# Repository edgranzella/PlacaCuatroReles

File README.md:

# Placa Cuatro Relés - Hardware y PCB 🚀

Este repositorio contiene el diseño completo de la placa de circuito impreso (PCB) desarrollado en **KiCad** para un sistema de conmutación y control de potencia de **4 canales de relés**.

---

## 📌 Características del Diseño
* **Canales de Potencia:** 4 relés independientes con aislamiento optoacoplado para proteger la etapa de control.
* **Bornes de Conexión:** Bloques de terminales de tornillo (Terminal Blocks) robustos para salidas de alta corriente (NA / NC / COM).
* **Etapa de Disparo:** Transistores/Optoacopladores dedicados por canal con diodos de libre circulación (flyback) integrados.
* **Indicadores Visuales:** LEDs de estado montados en placa para retroalimentación visual de la activación de cada canal.

---

## 🛠️ Especificaciones Técnicas de Fabricación
Configuración sugerida en base a las reglas de diseño (DRC) aplicadas en KiCad:

| Parámetro | Configuración Sugerida |
| :--- | :--- |
| **Capas (Layers)** | 2 Capas |
| **Grosor de la Placa** | 1.6 mm |
| **Ancho de Pistas** | Señales estándar / Pistas de potencia reforzadas |
| **Acabado Superficial** | HASL (with lead) o ENIG |

---

## 👥 Desarrollado por
* **Damian Granzella** - *Ingeniería de Hardware* - [edgranzella](https://github.com)

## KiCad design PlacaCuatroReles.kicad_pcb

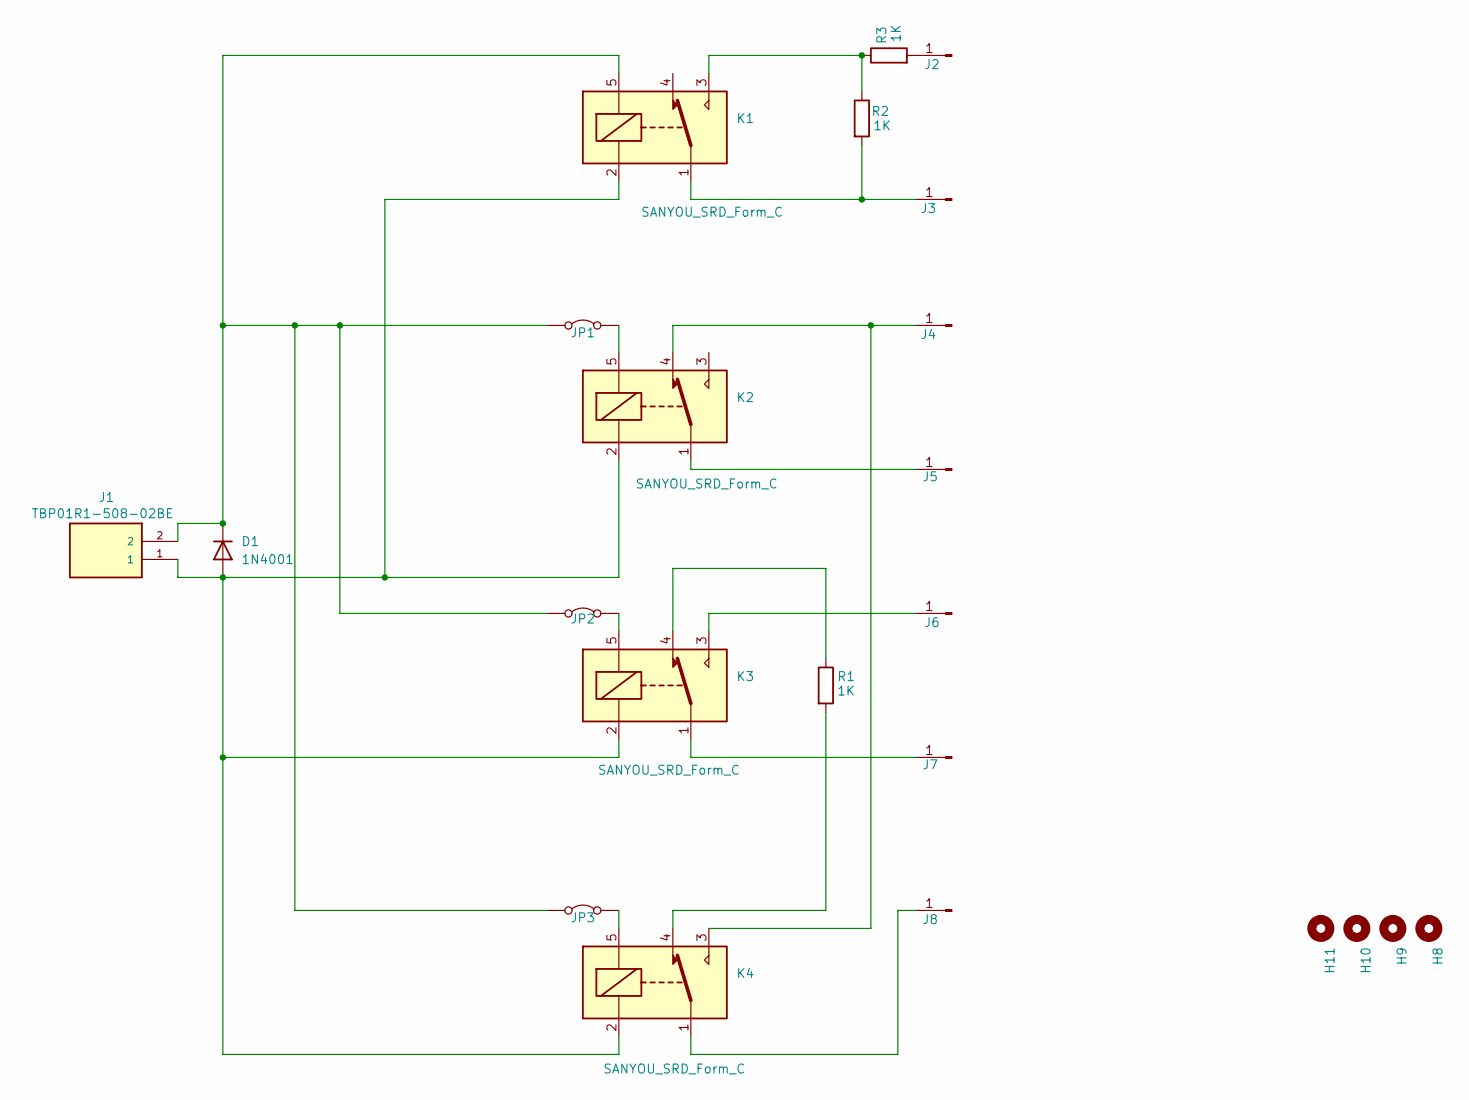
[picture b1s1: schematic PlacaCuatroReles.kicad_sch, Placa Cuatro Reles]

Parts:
D1: 1N4001; D_DO-41_SOD81_P10.16mm_Horizontal
H8, H9, H10, H11: MountingHole; MountingHole_4mm_Pad
J1: TBP01R1-508-02BE; TerminalBlock_Phoenix_PT-1,5-2-5.0-H_1x02_P5.00mm_Horizontal
J2, J3, J4, J5, J6, J7, J8: Conn_01x01_Pin; PinHeader_1x01_P2.54mm_Vertical
JP1, JP2, JP3: Jumper_2_Bridged; R_Bare_Metal_Element_L10mm
K1, K2, K3, K4: SANYOU_SRD_Form_C; Relay_SPDT_SANYOU_SRD_Series_Form_C
R1, R2, R3: 1K; R_Axial_DIN0207_L6.3mm_D2.5mm_P10.16mm_Horizontal

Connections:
unnamed: D1.2 (A), J1.1, K1.2, K2.2, K3.2, K4.2
unnamed: D1.1 (K), J1.2, JP1.1 (A), JP2.1 (A), JP3.1 (A), K1.5
unnamed: J2.1 (Pin_1_1), R3.2
unnamed: J3.1 (Pin_1_1), K1.1, R2.2
unnamed: J4.1 (Pin_1_1), K2.4, K4.3
unnamed: J5.1 (Pin_1_1), K2.1
unnamed: J6.1 (Pin_1_1), K3.3
unnamed: J7.1 (Pin_1_1), K3.1
unnamed: J8.1 (Pin_1_1), K4.1
unnamed: JP1.2 (B), K2.5
unnamed: JP2.2 (B), K3.5
unnamed: JP3.2 (B), K4.5
unnamed: K1.3, R2.1, R3.1
unnamed: K3.4, R1.1
unnamed: K4.4, R1.2

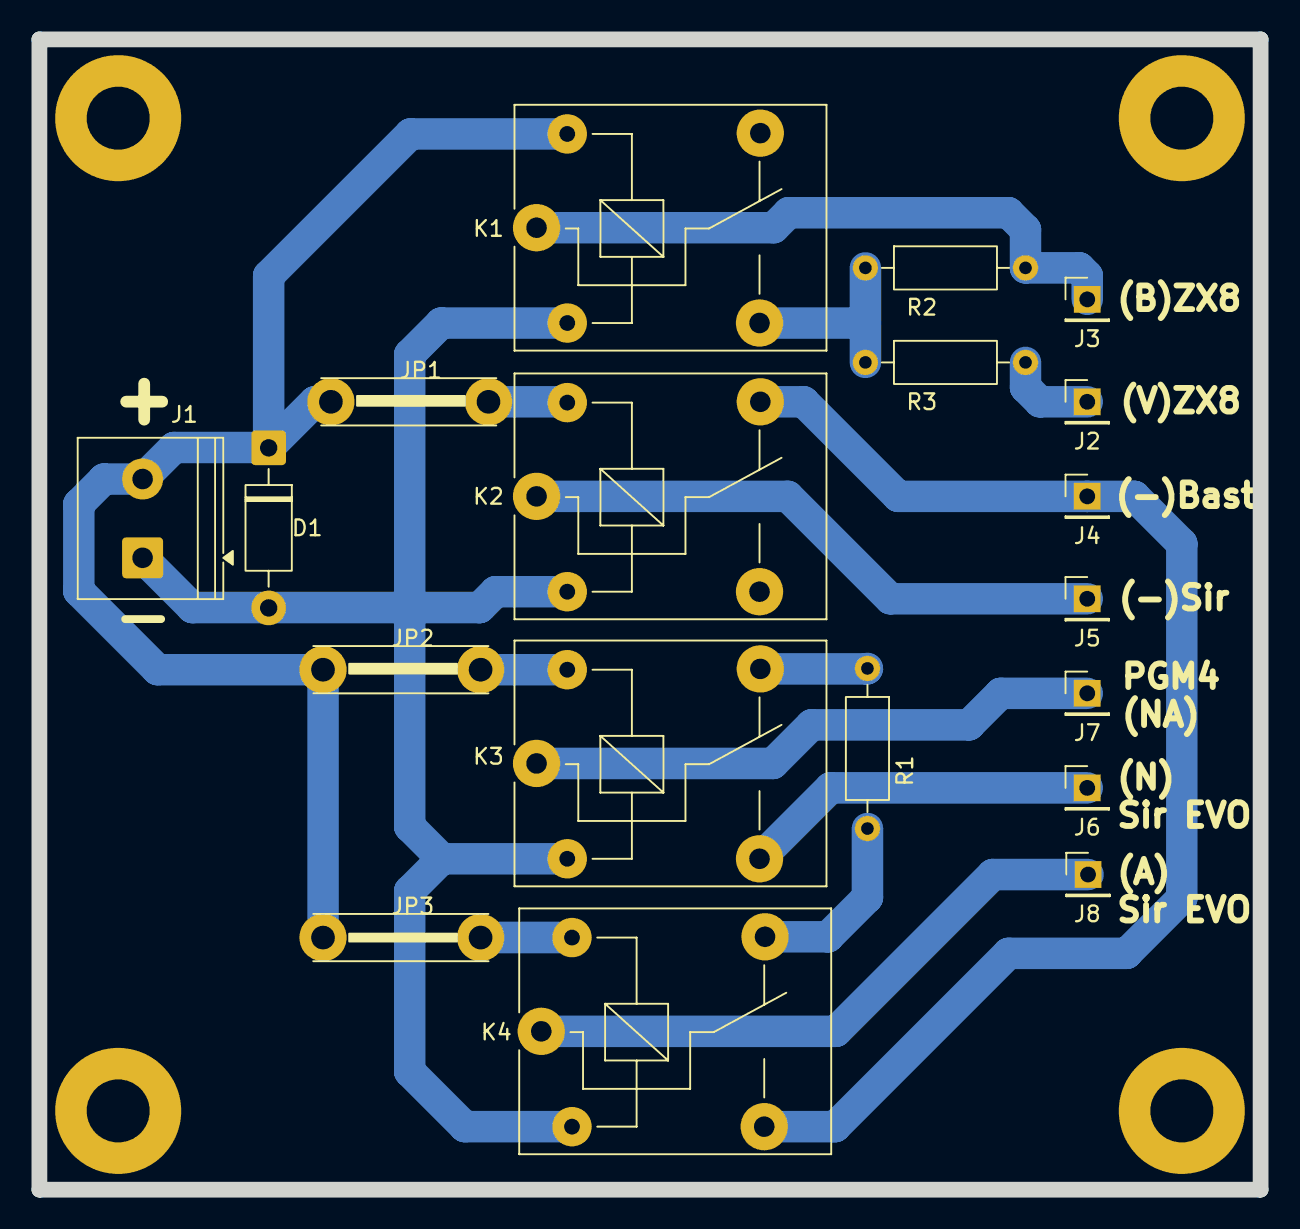
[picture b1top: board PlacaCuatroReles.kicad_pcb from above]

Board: 2 copper layers, 77.5 x 73.0 mm, 23 parts (0 on the bottom side), 15 nets.

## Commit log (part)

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2026-06-24 Hardware: Subir esquemáticos y diseño de PCB en KiCad
2026-06-24 Fix: Integrar contenido de .history de forma correcta
2026-06-24 Fix: Ignorar la carpeta de historial local .history
